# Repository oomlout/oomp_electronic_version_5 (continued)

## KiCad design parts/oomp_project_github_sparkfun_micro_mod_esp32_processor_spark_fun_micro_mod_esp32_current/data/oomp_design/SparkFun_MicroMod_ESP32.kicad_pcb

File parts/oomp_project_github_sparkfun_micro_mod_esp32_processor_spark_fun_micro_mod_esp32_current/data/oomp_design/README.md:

# OOMP KiCad design copy

Open `SparkFun_MicroMod_ESP32.kicad_pro` (or the `.kicad_pcb` / `.kicad_sch`) in KiCad. Local OOMP libraries are under `libraries/`. Original inputs are preserved in [../original/](../original/).

Only verified unchanged installed KiCad defaults were renamed. Modified, custom, unmatched and unavailable items remain unchanged. Soldering variants are never swapped during conversion. Existing pad coordinates, nets and UUIDs are preserved.

See [conversion_report.yaml](conversion_report.yaml) for every conversion and skip. Copy this directory before editing; regeneration refuses to overwrite edited design files.

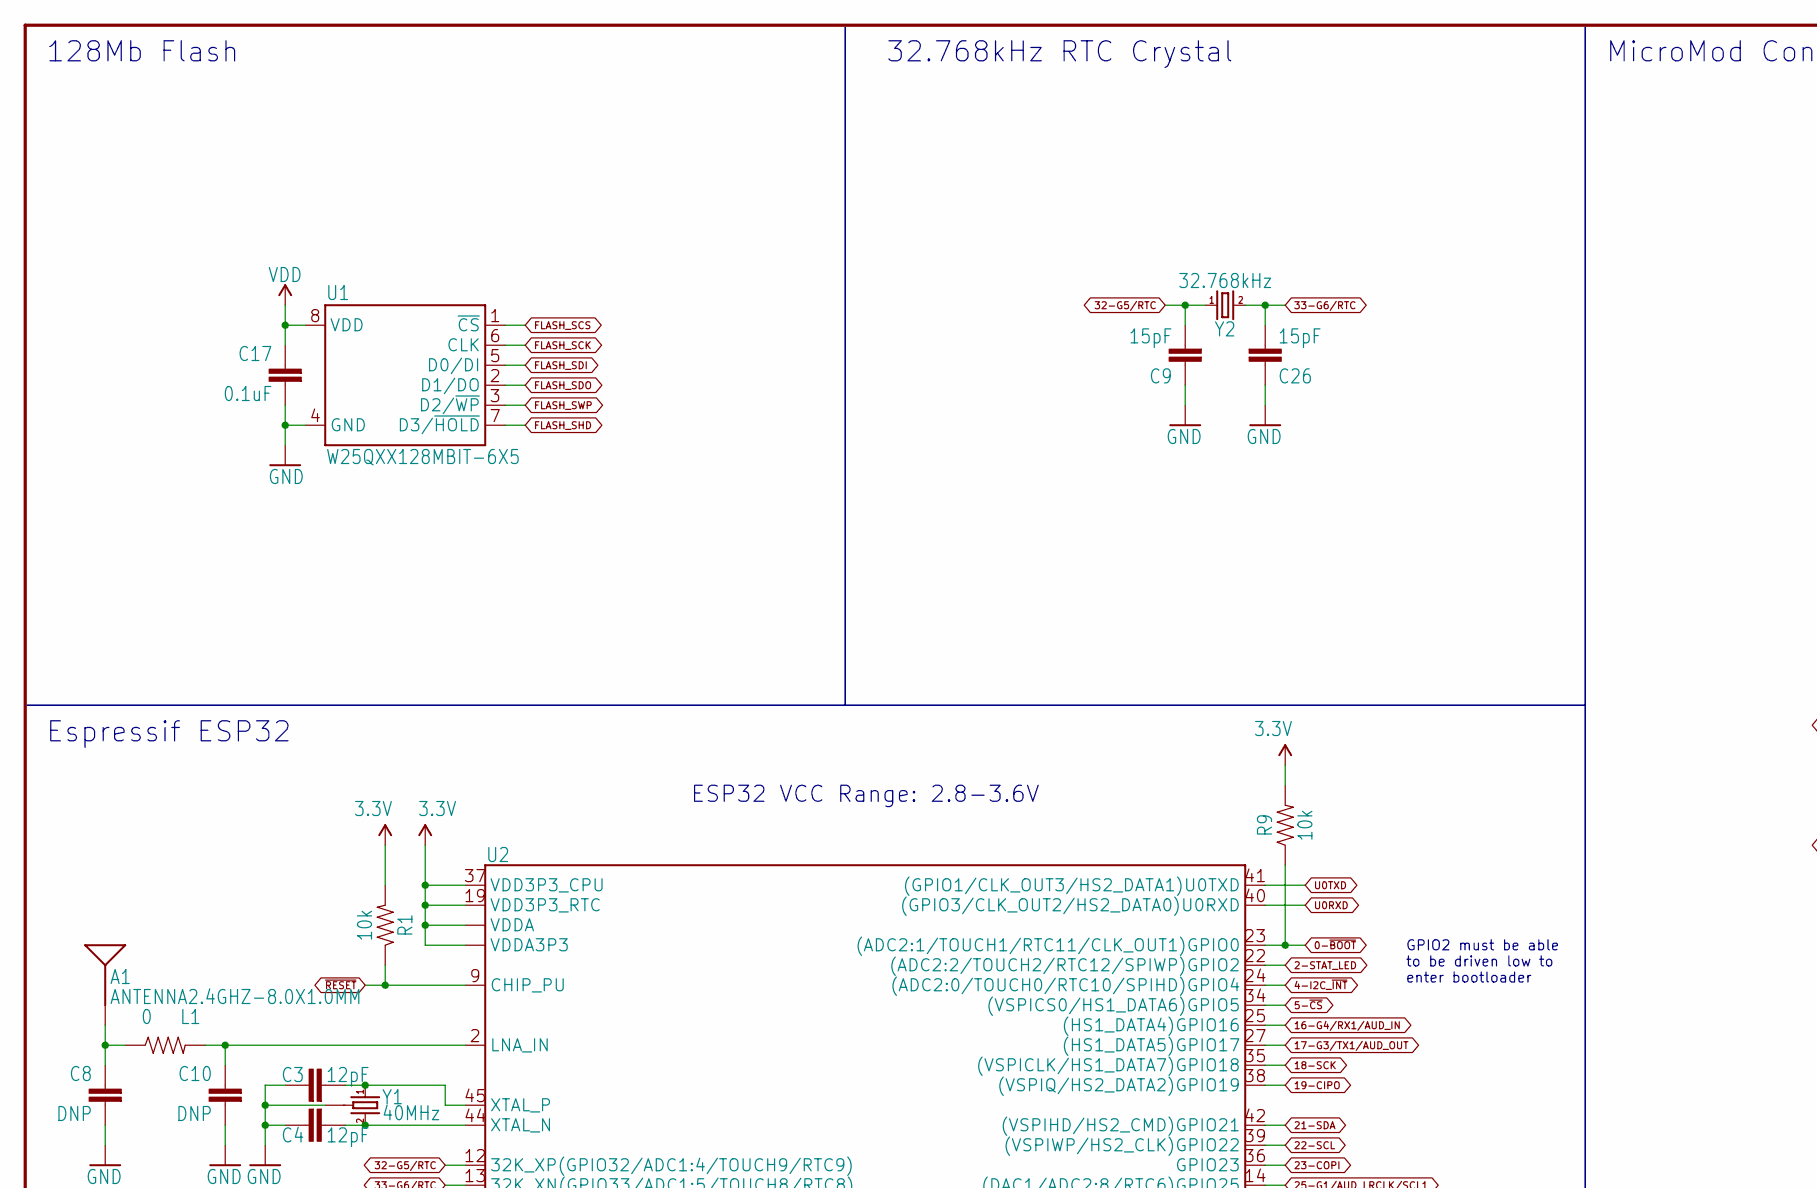
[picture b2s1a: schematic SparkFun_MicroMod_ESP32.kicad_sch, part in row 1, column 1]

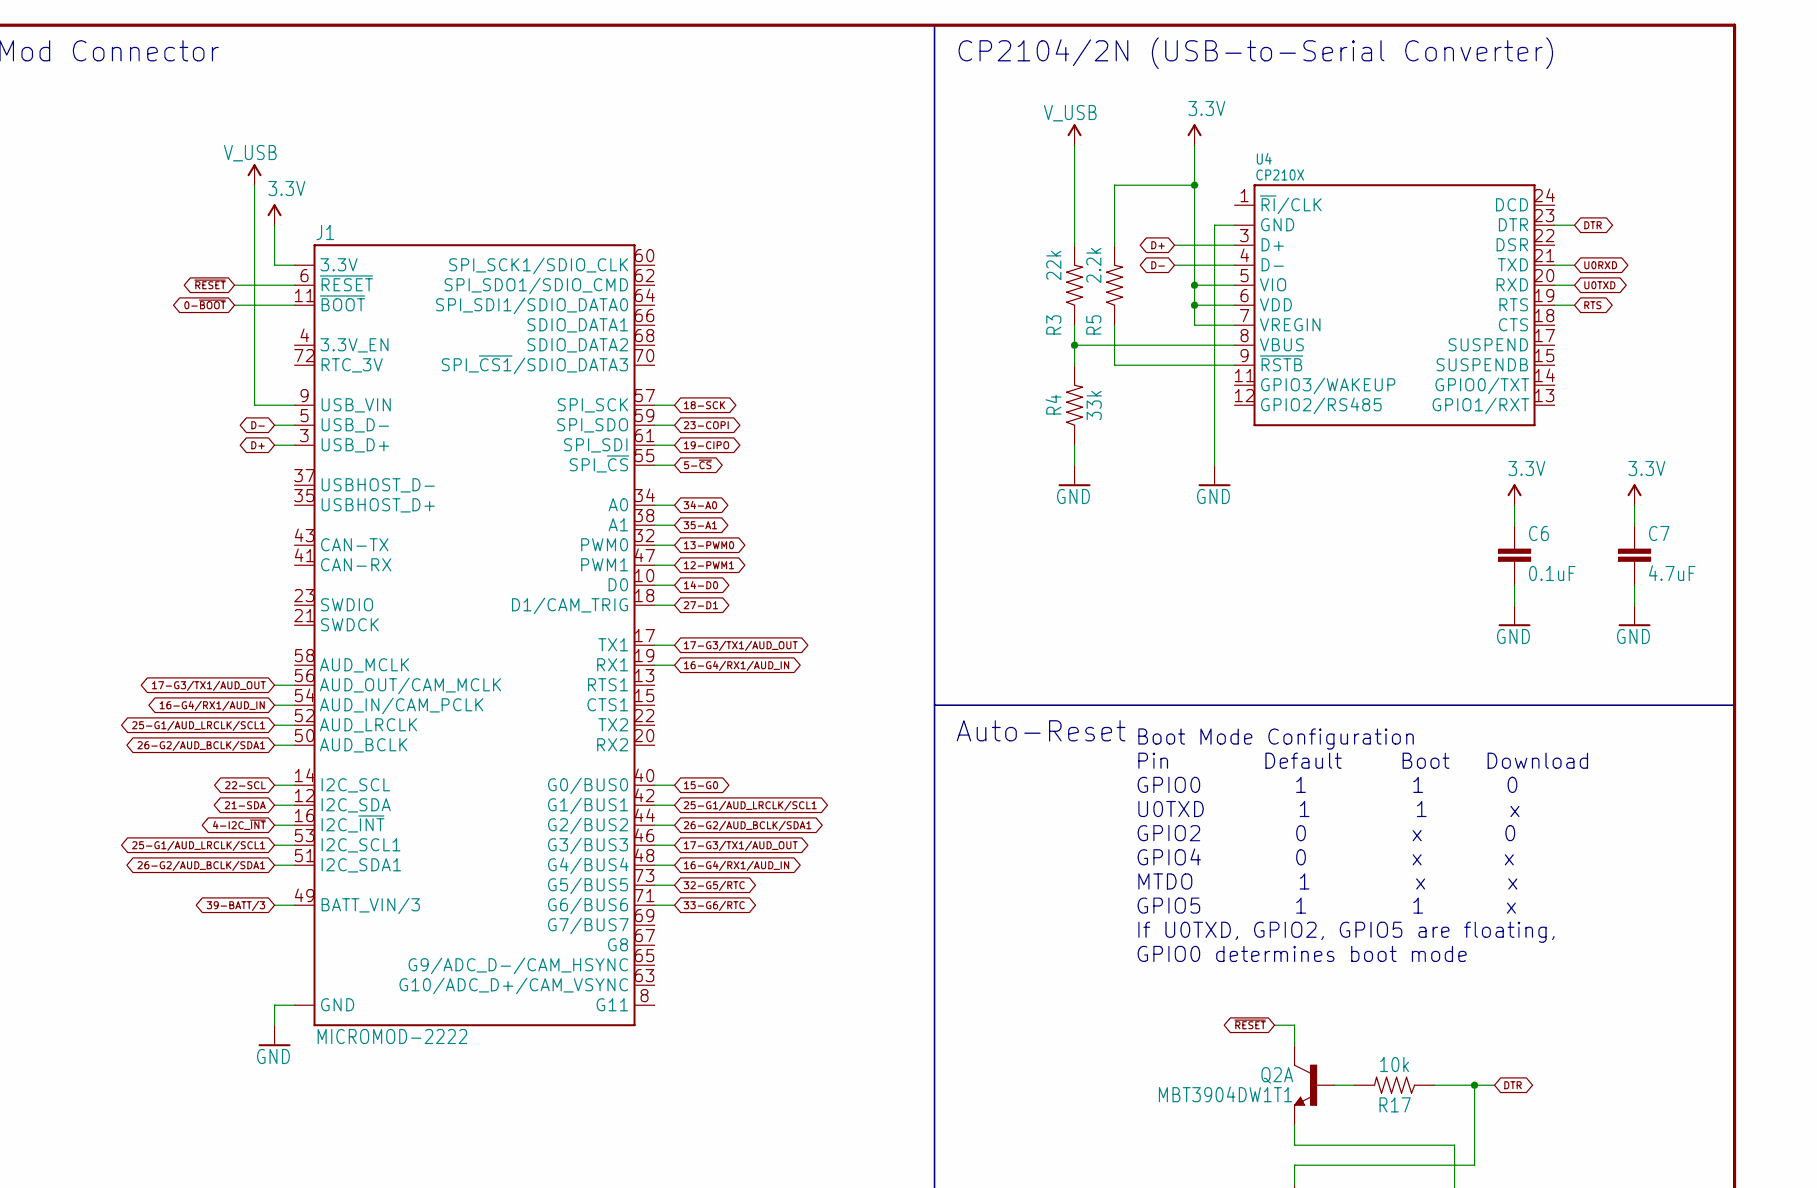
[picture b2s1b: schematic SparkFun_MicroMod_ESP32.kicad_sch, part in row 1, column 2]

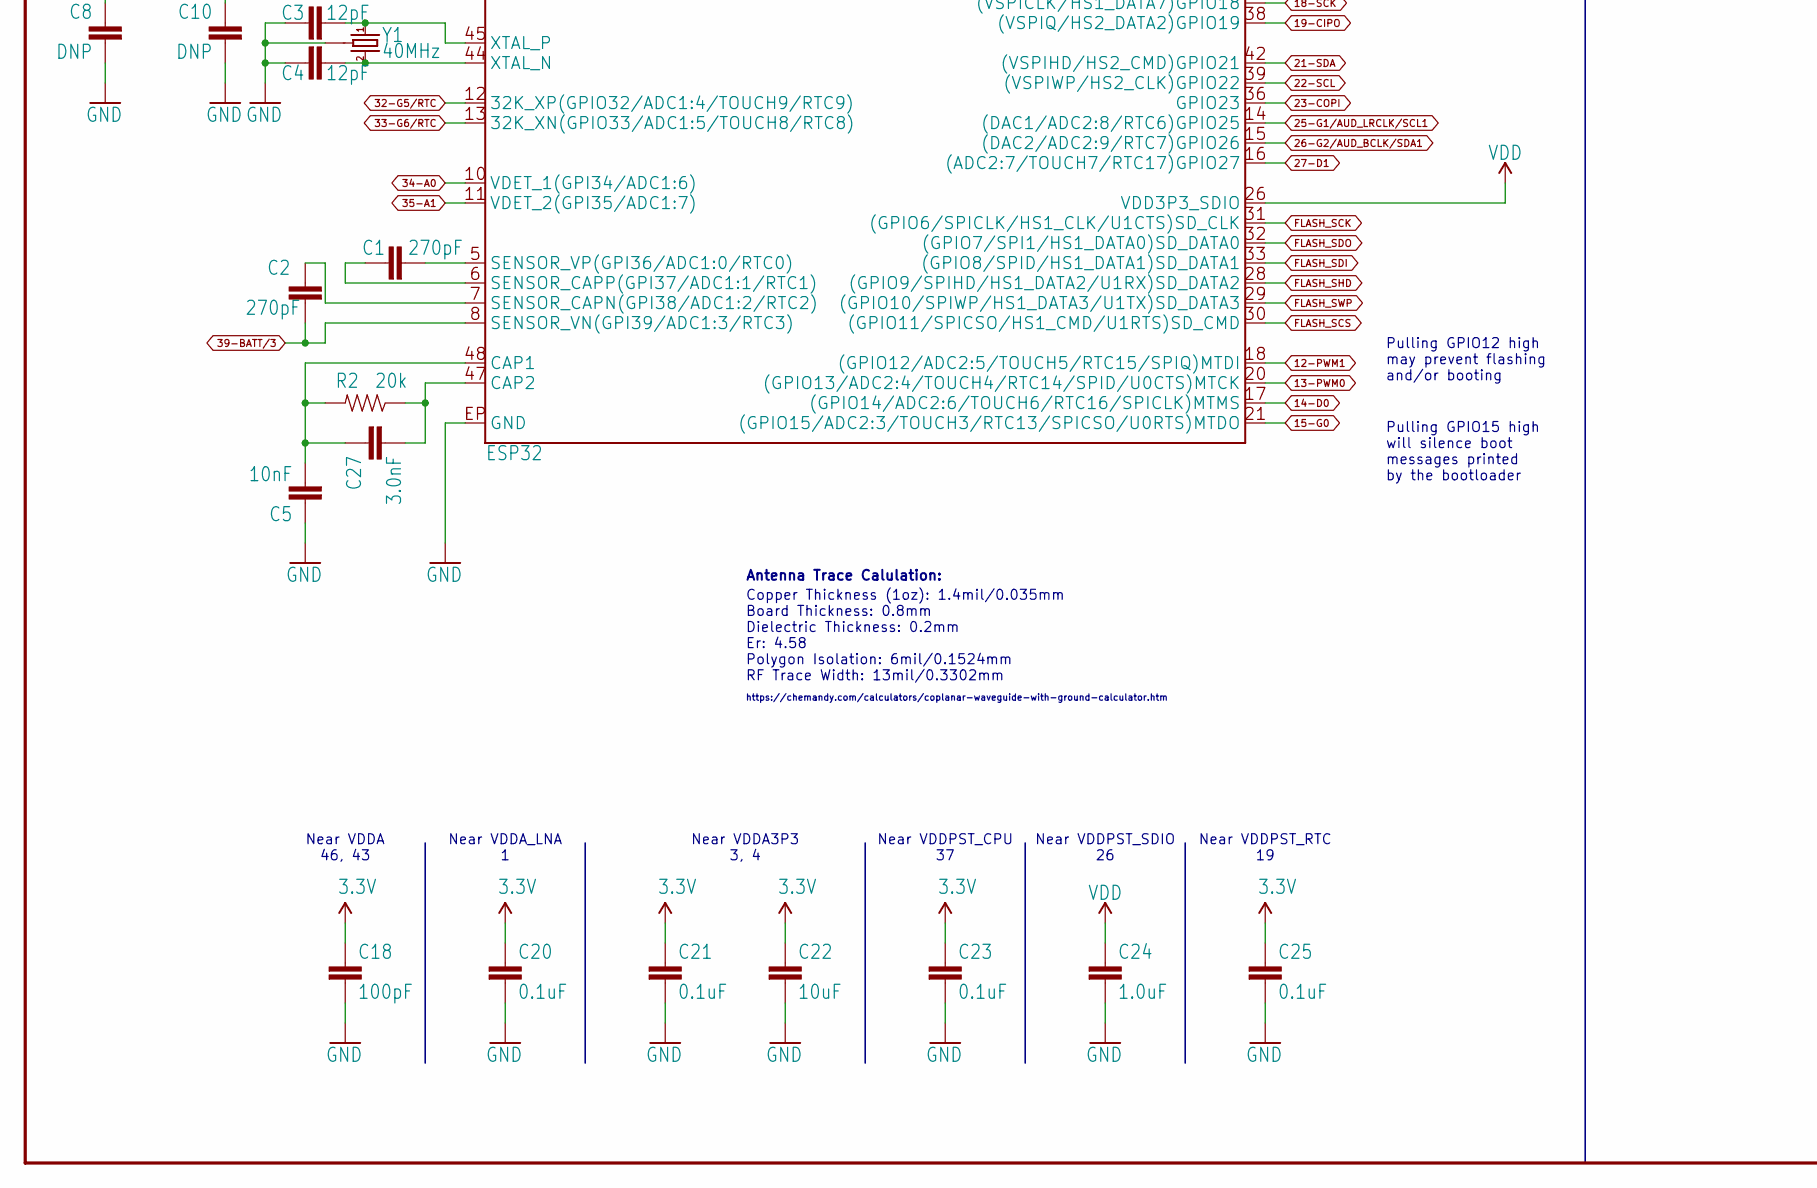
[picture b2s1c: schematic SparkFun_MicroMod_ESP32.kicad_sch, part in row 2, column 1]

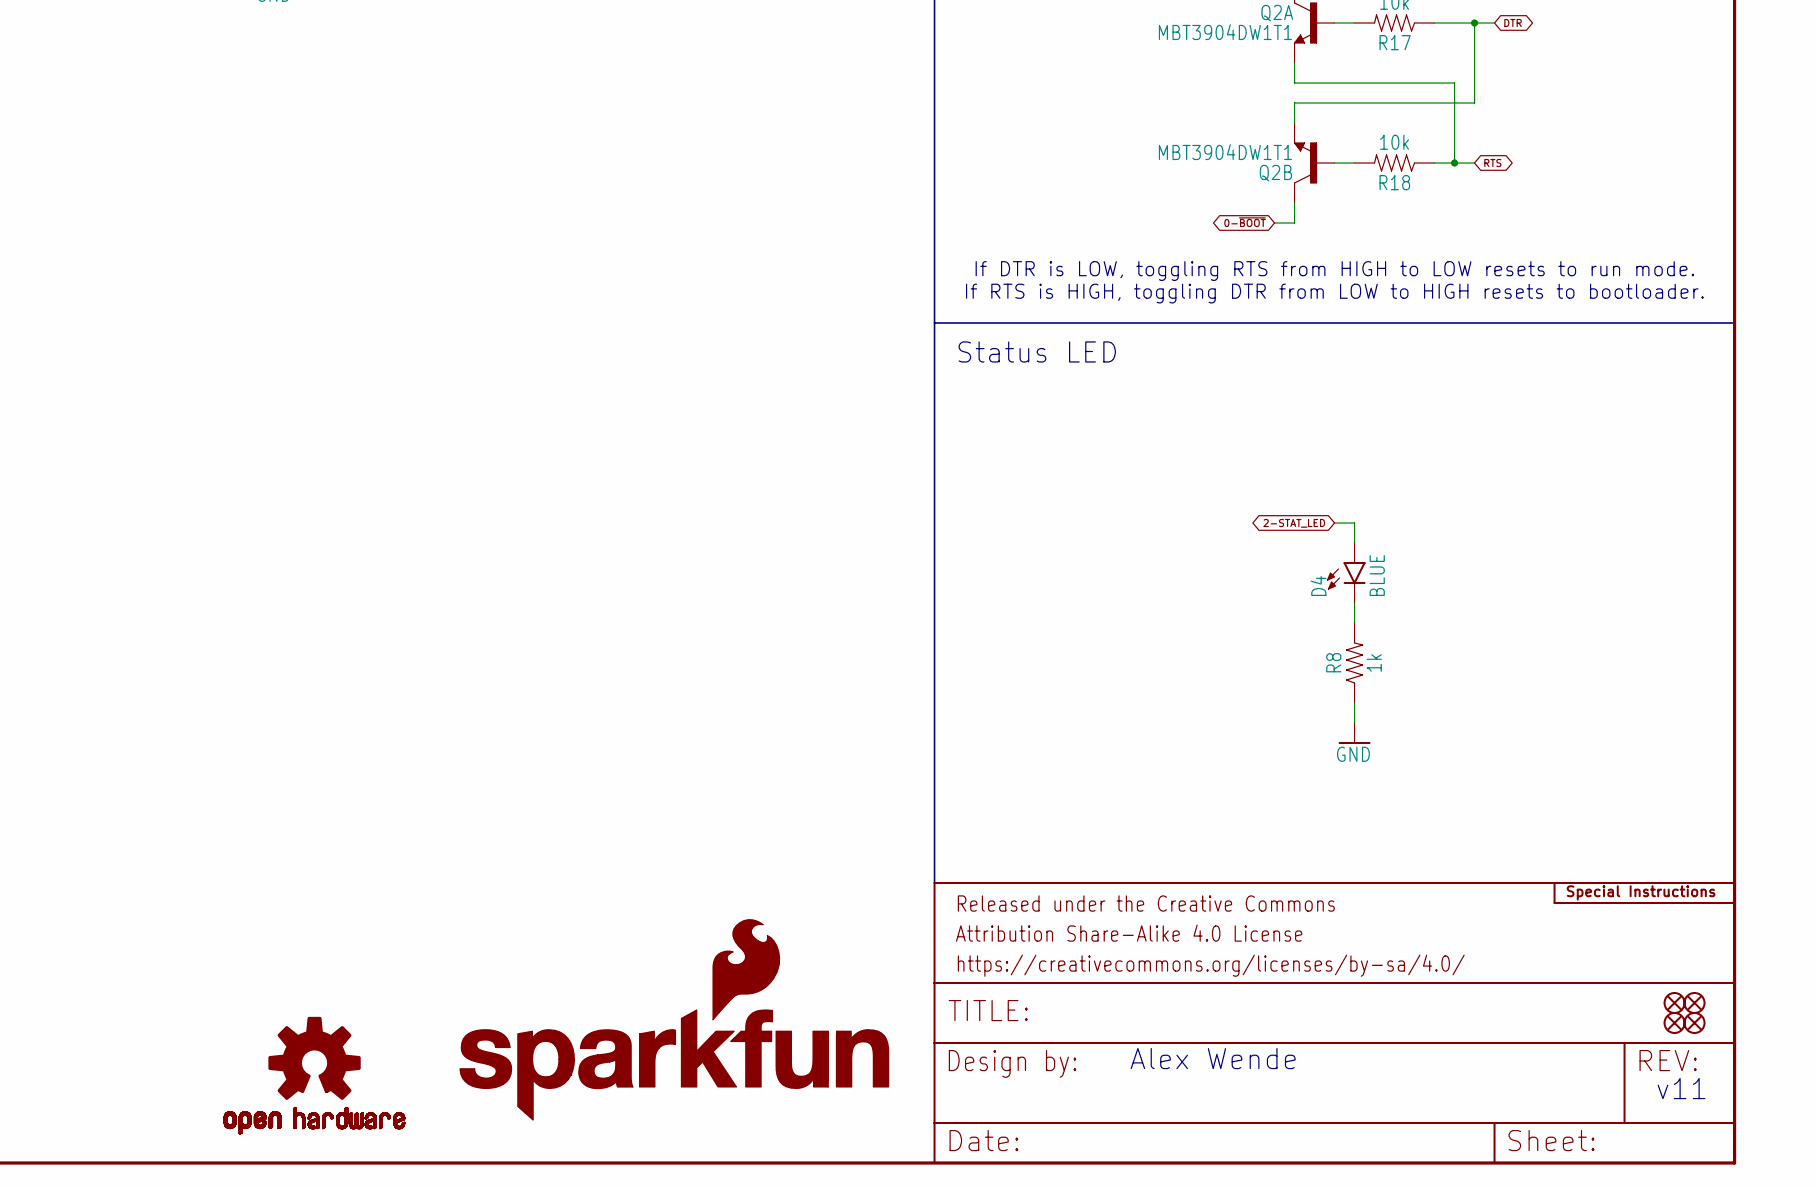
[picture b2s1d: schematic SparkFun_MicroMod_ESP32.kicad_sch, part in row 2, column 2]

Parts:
A1: ANTENNA2.4GHZ-8.0X1.0MM; ANT-2.4GHZ-8.0X1.0MM
C1, C2: 270pF; 0402-TIGHT
C3, C4: 12pF; 0402-TIGHT
C5: 10nF; 0402-TIGHT
C6, C17, C20, C21, C23, C25: 0.1uF; 0402-TIGHT
C7: 4.7uF; 0402-TIGHT
C8, C10: DNP; 0402-TIGHT
C9, C26: 15pF; 0402-TIGHT
C18: 100pF; 0402-TIGHT
C22: 10uF; 0402-TIGHT
C24: 1.0uF; 0402-TIGHT
C27: 3.0nF; 0402-TIGHT
D4: BLUE; LED-0603
FD1, FD2, FD3, FD4: FIDUCIALUFIDUCIAL; FIDUCIAL-MICRO
FRAME1: FRAME-LEDGER; CREATIVE_COMMONS
J1: MICROMOD-2222; M.2-CARD-E-22
L1: 0; 0402-TIGHT
LOGO1: SPECIAL_INSTRUCTIONS-ORDERING; ORDERING_INSTRUCTIONS
LOGO2: SFE_LOGO_NAME_FLAME.1_INCH; SFE_LOGO_NAME_FLAME_.1
LOGO3: OSHW-LOGOS; OSHW-LOGO-S
Q2: MBT3904DW1T1; SC70-6
R1, R9, R17, R18: 10k; 0402-TIGHT
R2: 20k; 0402-TIGHT
R3: 22k; 0402-TIGHT
R4: 33k; 0402-TIGHT
R5: 2.2k; 0402-TIGHT
R8: 1k; 0402-TIGHT
U1: W25QXX128MBIT-6X5; WSON-8-6X5
U2: ESP32; QFN48-0.4MM
U4: CP210X; QFN24
Y1: 40MHz; CRYSTAL-SMD-2X2.5MM
Y2: 32.768kHz; CRYSTAL-SMD-3.2X1.5MM

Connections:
0-~BOOT: J1.11 (~BOOT), Q2.6 (C), R9.1, U2.23 ((ADC2:1/TOUCH1/RTC11/CLK_OUT1)GPIO0)
2-STAT_LED: D4.A, U2.22 ((ADC2:2/TOUCH2/RTC12/SPIWP)GPIO2)
3.3V: C6.1, C7.1, C18.1, C20.1, C21.1, C22.1, C23.1, C25.1, J1.2 (3.3V), J1.74 (3.3V), R1.2, R5.2, R9.2, U2.1 (VDDA), U2.3 (VDDA3P3), U2.4 (VDDA3P3), U2.19 (VDD3P3_RTC), U2.37 (VDD3P3_CPU), U2.43 (VDDA), U2.46 (VDDA), U4.5 (VIO), U4.6 (VDD), U4.7 (VREGIN)
4-I2C_~INT: J1.16 (I2C_~INT), U2.24 ((ADC2:0/TOUCH0/RTC10/SPIHD)GPIO4)
5-~CS: J1.55 (SPI_~CS), U2.34 ((VSPICS0/HS1_DATA6)GPIO5)
12-PWM1: J1.47 (PWM1), U2.18 ((GPIO12/ADC2:5/TOUCH5/RTC15/SPIQ)MTDI)
13-PWM0: J1.32 (PWM0), U2.20 ((GPIO13/ADC2:4/TOUCH4/RTC14/SPID/U0CTS)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)
14-D0: J1.10 (D0), U2.17 ((GPIO14/ADC2:6/TOUCH6/RTC16/SPICLK)MTMS)
15-G0: J1.40 (G0/BUS0), U2.21 ((GPIO15/ADC2:3/TOUCH3/RTC13/SPICSO/U0RT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)
16-G4/RX1/AUD_IN: J1.19 (RX1), J1.48 (G4/BUS4), J1.54 (AUD_IN/CAM_PCLK), U2.25 ((HS1_DATA4)GPIO16)
17-G3/TX1/AUD_OUT: J1.17 (TX1), J1.46 (G3/BUS3), J1.56 (AUD_OUT/CAM_MCLK), U2.27 ((HS1_DATA5)GPIO17)
18-SCK: J1.57 (SPI_SCK), U2.35 ((VSPICLK/HS1_DATA7)GPIO18)
19-CIPO: J1.61 (SPI_SDI), U2.38 ((VSPIQ/HS2_DATA2)GPIO19)
21-SDA: J1.12 (I2C_SDA), U2.42 ((VSPIHD/HS2_CMD)GPIO21)
22-SCL: J1.14 (I2C_SCL), U2.39 ((VSPIWP/HS2_CLK)GPIO22)
23-COPI: J1.59 (SPI_SDO), U2.36 (GPIO23)
25-G1/AUD_LRCLK/SCL1: J1.42 (G1/BUS1), J1.52 (AUD_LRCLK), J1.53 (I2C_SCL1), U2.14 ((DAC1/ADC2:8/RTC6)GPIO25)
26-G2/AUD_BCLK/SDA1: J1.44 (G2/BUS2), J1.50 (AUD_BCLK), J1.51 (I2C_SDA1), U2.15 ((DAC2/ADC2:9/RTC7)GPIO26)
27-D1: J1.18 (D1/CAM_TRIG), U2.16 ((ADC2:7/TOUCH7/RTC17)GPIO27)
32-G5/RTC: C9.2, J1.73 (G5/BUS5), U2.12 (32K_XP(GPIO32/ADC1:4/TOUCH9/RTC9)), Y2.P$1 (1)
33-G6/RTC: C26.2, J1.71 (G6/BUS6), U2.13 (32K_XN(GPIO33/ADC1:5/TOUCH8/RTC8)), Y2.P$2 (2)
34-A0: J1.34 (A0), U2.10 (VDET_1(GPI34/ADC1:6))
35-A1: J1.38 (A1), U2.11 (VDET_2(GPI35/ADC1:7))
36: C1.2, U2.5 (SENSOR_VP(GPI36/ADC1:0/RTC0))
37: C1.1, U2.6 (SENSOR_CAPP(GPI37/ADC1:1/RTC1))
38: C2.1, U2.7 (SENSOR_CAPN(GPI38/ADC1:2/RTC2))
39-BATT/3: C2.2, J1.49 (BATT_VIN/3), U2.8 (SENSOR_VN(GPI39/ADC1:3/RTC3))
CAP_10N: C5.2, C27.1, R2.2, U2.48 (CAP1)
D+: J1.3 (USB_D+), U4.3 (D+)
D-: J1.5 (USB_D-), U4.4 (D-)
DTR: Q2.1 (E), R17.1, U4.23 (DTR)
FLASH_SCK: U1.6 (CLK), U2.31 ((GPIO6/SPICLK/HS1_CLK/U1CTS)SD_CLK)
FLASH_SCS: U1.1 (~CS), U2.30 ((GPIO11/SPICSO/HS1_CMD/U1RTS)SD_CMD)
FLASH_SDI: U1.5 (D0/DI), U2.33 ((GPIO8/SPID/HS1_DATA1)SD_DATA1)
FLASH_SDO: U1.2 (D1/DO), U2.32 ((GPIO7/SPI1/HS1_DATA0)SD_DATA0)
FLASH_SHD: U1.7 (D3/~HOLD), U2.28 ((GPIO9/SPIHD/HS1_DATA2/U1RX)SD_DATA2)
FLASH_SWP: U1.3 (D2/~WP), U2.29 ((GPIO10/SPIWP/HS1_DATA3/U1TX)SD_DATA3)
GND: C3.1, C4.1, C5.1, C6.2, C7.2, C8.2, C9.1, C10.2, C17.2, C18.2, C20.2, C21.2, C22.2, C23.2, C24.2, C25.2, C26.1, J1.1 (GND), J1.7 (GND), J1.33 (GND), J1.36 (GND), J1.39 (GND), J1.45 (GND), J1.75 (GND), J1.GND1 (GND), J1.GND2 (GND), J1.GND3 (GND), R4.1, R8.1, U1.4 (GND), U2.EP (GND), U4.2 (GND), U4.PAD (GND), Y1.P2 (GND), Y1.P4 (GND)
unnamed: D4.C, R8.2
unnamed: R3.1, R4.2, U4.8 (VBUS)
unnamed: R5.1, U4.9 (~RSTB)
unnamed: C27.2, R2.1, U2.47 (CAP2)
unnamed: A1.FEED, C8.1, L1.1
unnamed: C10.1, L1.2, U2.2 (LNA_IN)
unnamed: Q2.5 (B), R17.2
unnamed: Q2.2 (B), R18.2
unnamed: C3.2, U2.45 (XTAL_P), Y1.P1 (1)
unnamed: C4.2, U2.44 (XTAL_N), Y1.P3 (2)
RTS: Q2.4 (E), R18.1, U4.19 (RTS)
U0RXD: U2.40 ((GPIO3/CLK_OUT2/HS2_DATA0)U0RXD), U4.21 (TXD)
U0TXD: U2.41 ((GPIO1/CLK_OUT3/HS2_DATA1)U0TXD), U4.20 (RXD)
VDD: C17.1, C24.1, U1.8 (VDD), U2.26 (VDD3P3_SDIO)
V_USB: J1.9 (USB_VIN), R3.2
~RESET: J1.6 (~RESET), Q2.3 (C), R1.1, U2.9 (CHIP_PU)

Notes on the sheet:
Auto-Reset
CP2104/2N (USB-to-Serial Converter)
Alex Wende
Pulling GPIO12 high may prevent flashing and/or booting
Copper Thickness (1oz): 1.4mil/0.035mm Board Thickness: 0.8mm Dielectric Thickness: 0.2mm Er: 4.58 Polygon Isolation: 6mil/0.1524mm RF Trace Width: 13mil/0.3302mm
Espressif ESP32
Boot Mode Configuration Pin Default Boot Download GPIO0 1 1 0 U0TXD 1 1 x GPIO2 0 x 0 GPIO4 0 x x MTDO 1 x x GPIO5 1 1 x If U0TXD, GPIO2, GPIO5 are floating, GPIO0 determines boot mode
MicroMod Connector
Near VDDA3P3 3, 4
Antenna Trace Calulation:
Status LED
Near VDDA_LNA 1
https://chemandy.com/calculators/coplanar-waveguide-with-ground-calculator.htm
Near VDDPST_SDIO 26
Near VDDA 46, 43
ESP32 VCC Range: 2.8-3.6V
If DTR is LOW, toggling RTS from HIGH to LOW resets to run mode. If RTS is HIGH, toggling DTR from LOW to HIGH resets to bootloader.
32.768kHz RTC Crystal
GPIO2 must be able to be driven low to enter bootloader
Near VDDPST_CPU 37
Pulling GPIO15 high will silence boot messages printed by the bootloader
128Mb Flash
Near VDDPST_RTC 19
v11

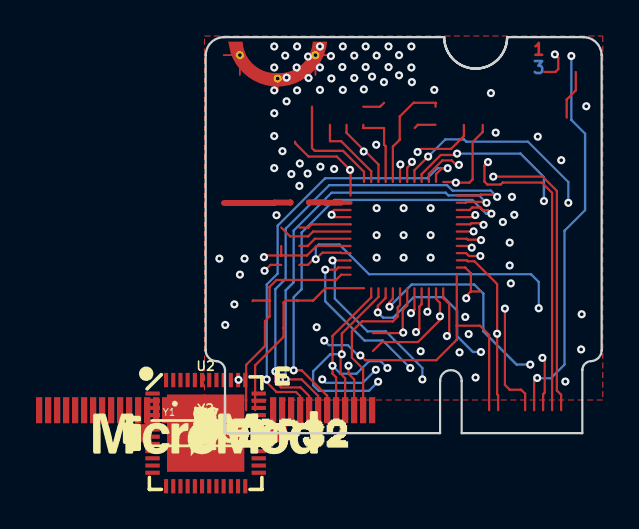
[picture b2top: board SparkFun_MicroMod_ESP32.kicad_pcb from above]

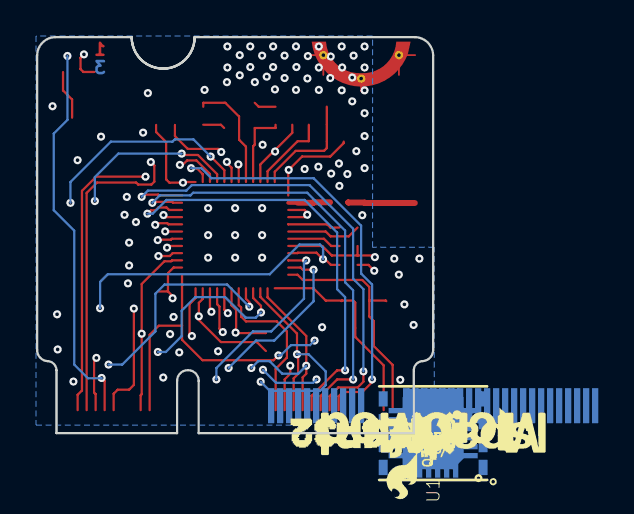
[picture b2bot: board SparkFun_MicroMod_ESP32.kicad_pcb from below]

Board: 4 copper layers, 22.0 x 22.0 mm, 53 parts (18 on the bottom side), 54 nets.

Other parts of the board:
U$1: STAT0
U$2, U$6: MICROMOD_LOGO_.5
U$3, U$7: ESP321
U$4: SFE_LOGO_FLAME_.1

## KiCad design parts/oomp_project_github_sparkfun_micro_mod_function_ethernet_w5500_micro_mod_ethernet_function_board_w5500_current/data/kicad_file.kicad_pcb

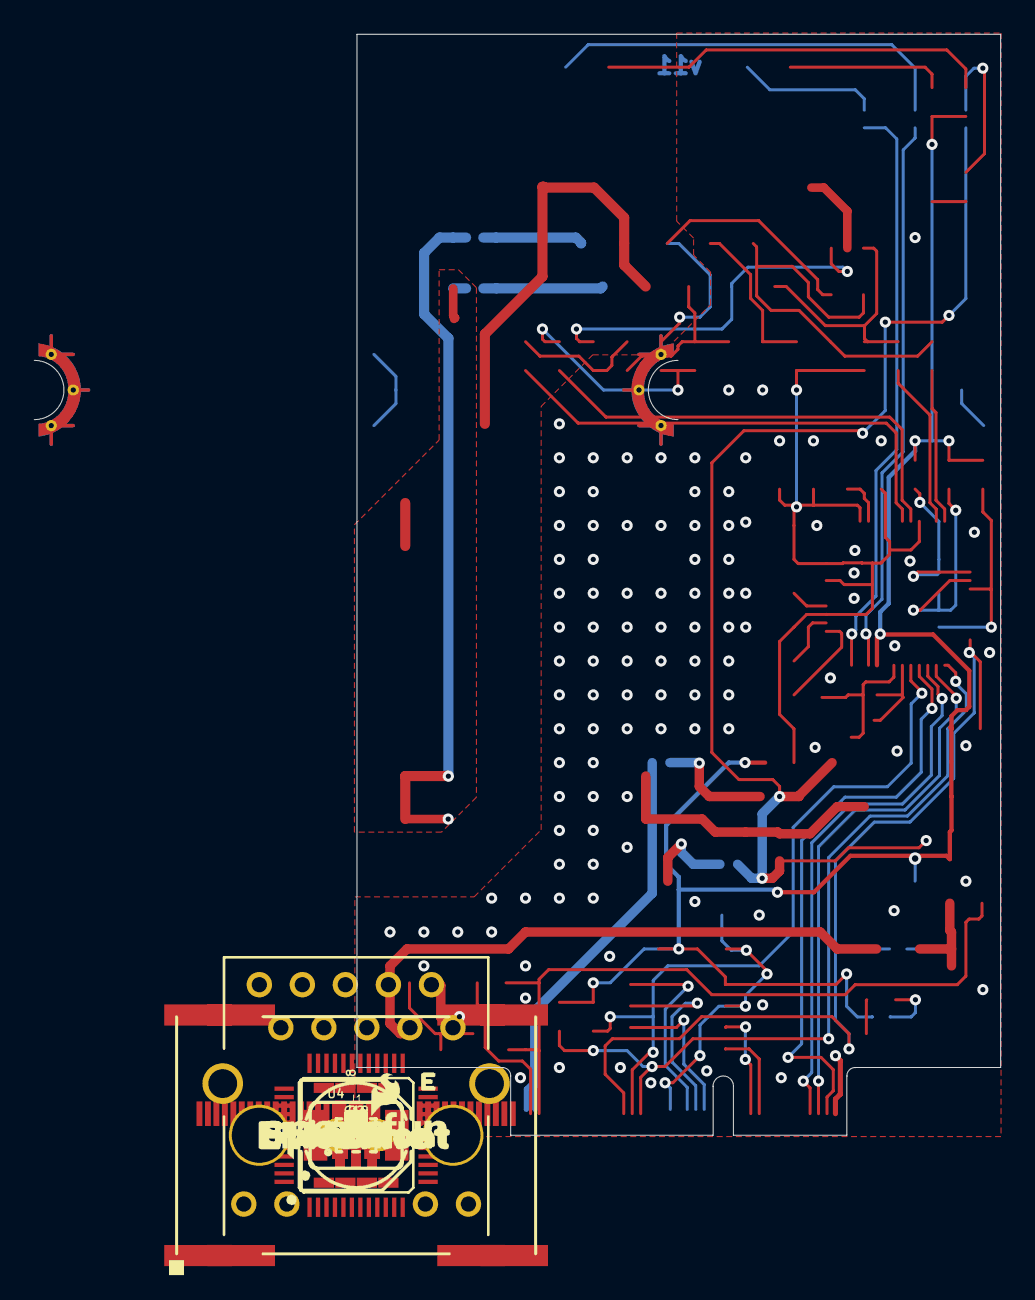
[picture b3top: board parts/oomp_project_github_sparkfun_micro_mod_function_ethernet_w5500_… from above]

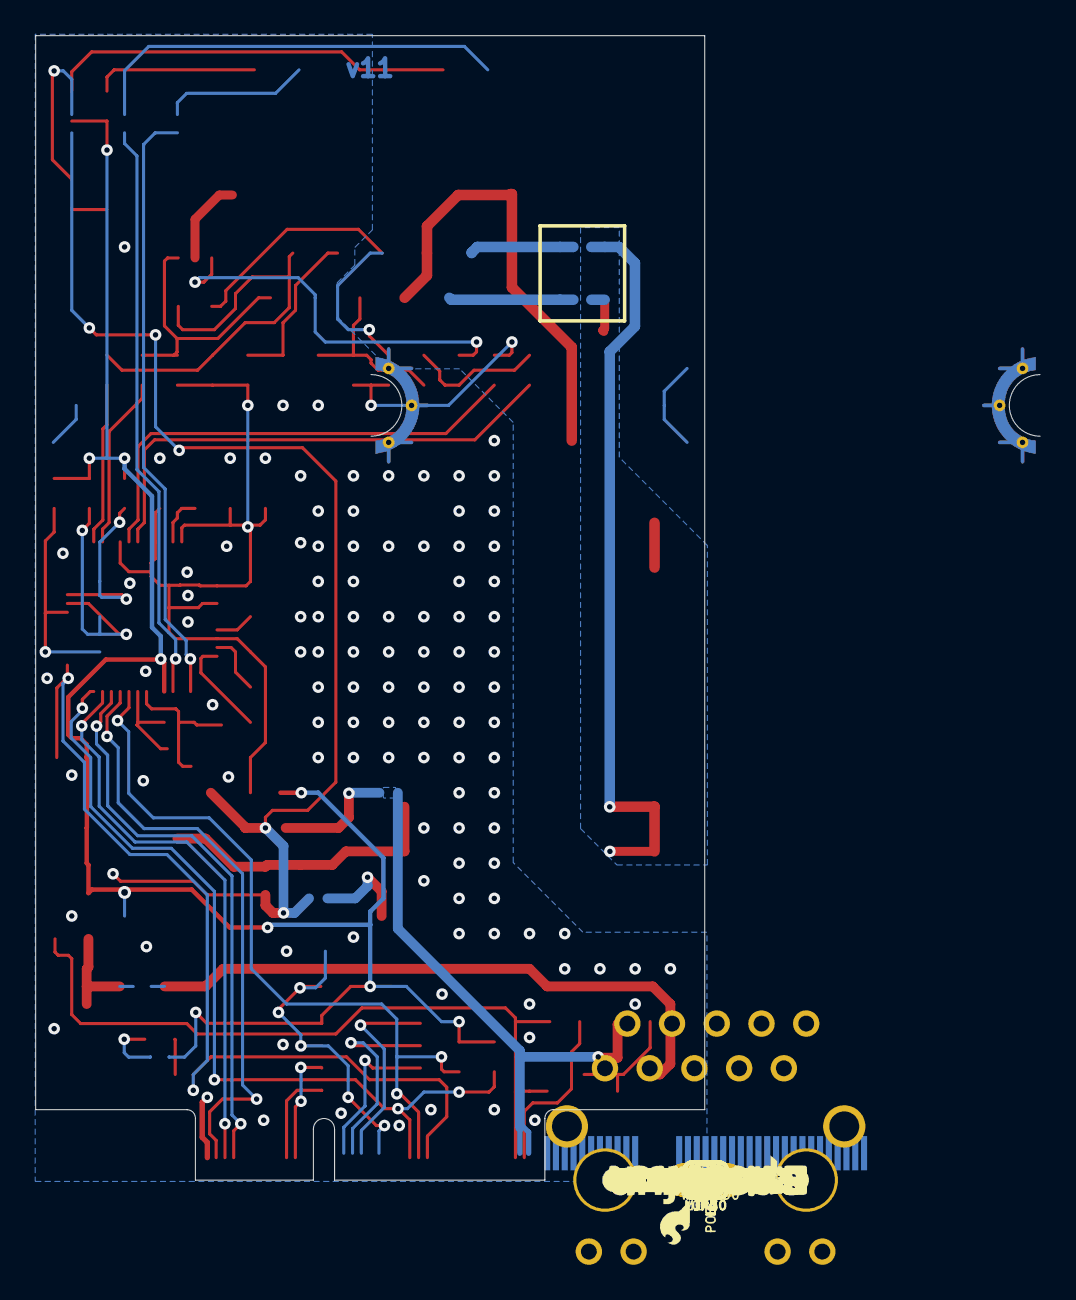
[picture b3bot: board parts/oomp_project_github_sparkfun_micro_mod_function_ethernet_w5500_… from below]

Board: 2 copper layers, 38.0 x 65.0 mm, 117 parts (38 on the bottom side), 61 nets.

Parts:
C1, C2, C3, C4, C10, C11, C12, C14, C15: 0.1uF; 0603
C5, C6: 10pF; 0603
C7, C25, C26: 10uF; 0805
C8: 100uF; PANASONIC_D
C9, C16: 10uF; 0603
C13, C24: 1.0uF; 0603
C17, C20: 10nF; 0603
C18: 4.7uF; 0603
C19: 1nF; 1206
C21, C22: 6.8nF; 0603
C23: 22nF; 0603
D1: 3A/10V/280mV; SOD-323
D2: RED; LED-0603
D5: Yellow; LED-0603
D7: DT1042-04SO; SOT-23-6
FB2: 470Ω; 0603
FD1, FD2, FD3, FD4: FIDUCIALUFIDUCIAL; FIDUCIAL-MICRO
FRAME1: FRAME-LEDGER; CREATIVE_COMMONS
ISO1, ISO2: JUMPER-COMBO_2_NC_TRACE; COMBO-JUMPER_2_NC_TRACE
J1: MAGJACK-POE; MAGJACK-SYM_LED
J11: MICROMOD_STANDARD; M.2-CARD-E-22_FUNCTION_STANDARD
JP1, JP2, JP3, JP5: JUMPER-SMT_2_NO_SILK; SMT-JUMPER_2_NO_SILK
L1: 2.2uH; 0805-WIDE
LED1, LED2: JUMPER-SMT_2_NC_TRACE_SILK; SMT-JUMPER_2_NC_TRACE_SILK
LOAD0: JUMPER-SMT_2_NC_TRACE_SILK; SMT-JUMPER_2_NC_TRACE_SILK
LOGO1, LOGO4: SFE_LOGO_NAME_FLAME.1_INCH; SFE_LOGO_NAME_FLAME_.1
LOGO2: SPECIAL_INSTRUCTIONS-ORDERING; ORDERING_INSTRUCTIONS
LOGO3: OSHW-LOGOMINI; OSHW-LOGO-MINI
MEAS0: JUMPER-COMBO_2_NC_TRACE; COMBO-JUMPER_2_NC_TRACE
POE0: SMT-JUMPER_2_NC_TRACE_SILK
POE_LED0: JUMPER-SMT_2_NC_TRACE_SILK; SMT-JUMPER_2_NC_TRACE_SILK
PWR_LED0: JUMPER-SMT_2_NC_TRACE_SILK; SMT-JUMPER_2_NC_TRACE_SILK
Q1: 220mA/50V/3.5Ω; SOT23-3
Q5: 20V/4.2A/52mΩ/1.4W; SOT23-3
R1: 1M; 0603
R2: 49.9 1/2W; 1206
R3, R5, R11, R25: 1k; 0603
R4, R6, R7, R9, R10, R12, R22, R23, R24, R30: 10k; 0603
R8: 12.4k; 0603
R13, R18, R19, R20: 49.9; 0603
R14, R15, R16, R17: 33; 0603
R21: 10; 0603
TP1: TEST-POINT3X4; PAD.03X.04
U1: EEPROM; SO08
U3: W5500; LQFP-48
U4: 3.3V; SOT23-5
U5: POE_PSU-DP990X; DP990X
U$1, U$17: ETHERNET0
U$2, U$18: #POE#0
U$3: #POWER_CARRIER#0
U$5: #DUMMY_LOAD#0
U$6: #WP#0
U$7: PWR0
U$8: #ACT#0
U$9: POE0
U$12: #LNK#1
U$13: #PMODE#0
U$14: 01
U$15: 12
U$16: 23
U$19: #0
U$20: CAUTION#0
U$21: HOT#1
U$22: #PWR#0
U$23: #_POE#0
U$24: PWR1
U$25: #1
U$26, U$27: FUNCTION0
U$28: #MEAS#3
U$37, U$63: MICROMOD_LOGO_.35
Y1: 25MHz; CRYSTAL-SMD-2.0X1.6MM

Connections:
3.3V: C1.1, C4.1, C9.1, C24.1, FB2.1, PWR_LED0.2, R3.2, R4.2, R5.2, R9.2, R10.2, R12.2, R22.1, R23.2, R24.2, TP1.1, U1.8, U3.28, U4.5
3.3V_IN: J11.73, R6.1
5V: C3.1, C13.1, MEAS0.2, MEAS0.4, U4.1
5V_FILTER: C26.1, D1.A, L1.2, LOAD0.2, POE_LED0.2
5V_RAW: C7.1, C8.+, C25.1, L1.1, U5.1, U5.2
A0: J11.36, U1.1
A1: J11.34, U1.2
A2: J11.32, U1.3
ACT_LED: LED2.2, U3.27
ETH_~CS: J11.49, R23.1, U3.32
ETH_~INT: J11.47, R4.1, U3.36
ETH_~RST: J11.51, R24.1, U3.37
EWP: J11.40, JP5.2, R22.2, U1.7
GND: C1.2, C2.2, C3.2, C4.2, C5.2, C6.2, C7.2, C8.-, C9.2, C10.2, C11.2, C12.2, C13.2, C14.2, C15.2, C16.2, C17.2, C18.2, C19.2, C20.2, C23.2, C24.2, C25.2, C26.2, D2.C, D5.C, J11.1, J11.33, J11.39, J11.45, J11.75, J11.GND1, J11.GND2, J11.GND3, J11.GND4, J11.GND5, J11.GND6, JP1.1, JP2.1, JP3.1, JP5.1, Q1.2, R2.1, R8.1, R30.1, U1.4, U3.3, U3.9, U3.14, U3.16, U3.19, U3.29, U3.48, U4.2, U5.3
GND-ISO: C19.1, D7.2, J1.7, J1.8, J1.S1, J1.S2
I2C_SCL: J11.21, U1.6
I2C_SDA: J11.19, U1.5
LINK_LED: LED1.2, U3.25
unnamed: C5.1, R1.1, U3.31, Y1.1
unnamed: C6.1, R1.2, U3.30, Y1.3
unnamed: J1.14, LED2.1
unnamed: J1.12, LED1.1
unnamed: D5.A, R11.1
unnamed: POE_LED0.1, R11.2
unnamed: D1.C, POE0.1
unnamed: J1.13, R5.1
unnamed: LOAD0.1, R2.2
unnamed: J1.11, R3.1
unnamed: Q1.3, Q5.1, R7.1
unnamed: R8.2, U3.10
unnamed: C17.1, U3.22
unnamed: C18.1, U3.20
unnamed: R30.2, U3.23
unnamed: PWR_LED0.1, R25.2
unnamed: D2.A, R25.1
PMODE0: JP1.2, R9.1, U3.45
PMODE1: JP2.2, R10.1, U3.44
PMODE2: JP3.2, R12.1, U3.43
PW1+: ISO1.2, ISO1.4, U5.5, U5.6
PW1-: ISO2.2, ISO2.4, U5.7, U5.8
PW+: ISO1.1, ISO1.3, J1.9
PW-: ISO2.1, ISO2.3, J1.10
PWR_EN: J11.71, Q1.1, R6.2, U4.3
RCT: C20.1, J1.5, R13.1, R18.1
RD+: C22.2, D7.3, J1.3
RD-: C21.2, D7.4, J1.6
RXN: R17.1, U3.5
RXN1: C21.1, R17.2, R18.2
RXP: R16.1, U3.6
RXP1: C22.1, R13.2, R16.2
SPI_CIPO: J11.7, U3.34
SPI_COPI: J11.5, U3.35
SPI_SCK: J11.3, U3.33
TCT: C23.1, J1.4, R21.1
TD+: D7.1, J1.1, R14.2, R19.1
TD-: D7.6, J1.2, R15.2, R20.1
TXN: R15.1, U3.1
TXP: R14.1, U3.2
VCC: MEAS0.1, MEAS0.3, Q5.3
VCCA: C2.1, C10.1, C11.1, C12.1, C14.1, C15.1, C16.1, FB2.2, R19.2, R20.2, R21.2, U3.4, U3.8, U3.11, U3.15, U3.17, U3.21
VCC_IN: J11.72, J11.74, POE0.2, Q5.2, R7.2

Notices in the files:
parts/oomp_project_github_sparkfun_micro_mod_data_logging_carrier_micro_mod_datalogging_carrier_board_current/data/original/kicad_file.kicad_sch:
Released under the Creative Commons
https://creativecommons.org/licenses/by-sa/4.0
parts and their libraries:
Released under the Creative Commons Attribution Share-Alike 4.0 License
